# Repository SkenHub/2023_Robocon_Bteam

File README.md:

# 2023_Robocon_Bteam
2023年高専ロボコン「もぎもぎ！フルーツＧＯラウンド」Bチーム
## メンバー
*  機械　ヒロハタ，金子，入谷，斉藤，神鍋 ,今井
*  制御　野口，川崎，笹渕，川口，黒住，佐谷  
*  回路　中井，岩井　
*  1年　北嶋，真志取  
* メイン：野口、川崎，金子
* ピット：渡邉，入谷，北嶋，廣畑，真志取

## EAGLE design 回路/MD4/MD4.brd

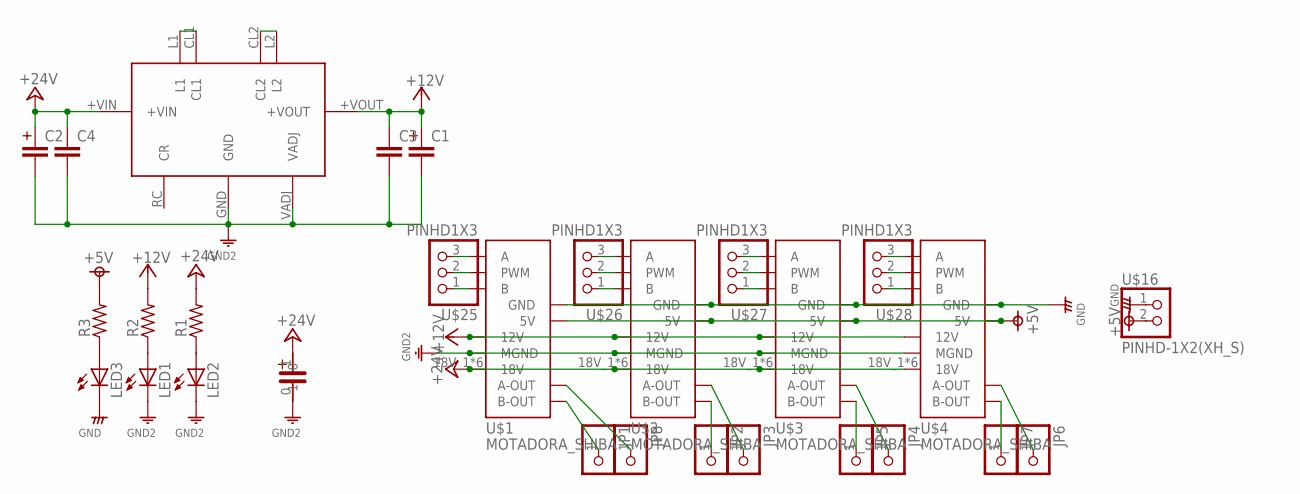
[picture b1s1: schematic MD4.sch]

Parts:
C1, C2: CAPACITOR-1U; C_1U
C3, C4: MLCC-5; MLCC_50
CAPACITOR1: CAPACITOR
JP1, JP2, JP3, JP4, JP5, JP6, JP7, JP8: PINHD-1X1; 1X01
LED1, LED2, LED3: LED3MM
R1, R2, R3: RESISTORS-3; R_0.3
U$1, U$2, U$3, U$4: MOTADORA_SHIBA
U$10: HPH12002M
U$16: PINHD-1X2(XH_S); 1X2(XH-S)
U$25, U$26, U$27, U$28: PINHD1X3; 1X3(XH)

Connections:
+5V: R3.2, U$1.5V, U$1.5V_2 (5V), U$2.5V, U$2.5V_2 (5V), U$3.5V, U$3.5V_2 (5V), U$4.5V, U$4.5V_2 (5V), U$16.2
+12V: C1.P$1 (1), C3.1, R2.2, U$1.12V_1 (12V), U$1.12V_2 (12V), U$1.12V_3 (12V), U$1.12V_4 (12V), U$1.12V_5 (12V), U$1.12V_6 (12V), U$2.12V_1 (12V), U$2.12V_2 (12V), U$2.12V_3 (12V), U$2.12V_4 (12V), U$2.12V_5 (12V), U$2.12V_6 (12V), U$3.12V_1 (12V), U$3.12V_2 (12V), U$3.12V_3 (12V), U$3.12V_4 (12V), U$3.12V_5 (12V), U$3.12V_6 (12V), U$4.12V_1 (12V), U$4.12V_2 (12V), U$4.12V_3 (12V), U$4.12V_4 (12V), U$4.12V_5 (12V), U$4.12V_6 (12V), U$10.+VOUT
GND: LED3.K (C), U$1.GND, U$1.GND2 (GND), U$2.GND, U$2.GND2 (GND), U$3.GND, U$3.GND2 (GND), U$4.GND, U$4.GND2 (GND), U$16.1
GND12: C1.P$2 (2), C2.P$2 (2), C3.2, C4.2, CAPACITOR1.0, LED1.K (C), LED2.K (C), U$1.MGND_1 (MGND), U$1.MGND_2 (MGND), U$1.MGND_3 (MGND), U$1.MGND_4 (MGND), U$1.MGND_5 (MGND), U$1.MGND_6 (MGND), U$2.MGND_1 (MGND), U$2.MGND_2 (MGND), U$2.MGND_3 (MGND), U$2.MGND_4 (MGND), U$2.MGND_5 (MGND), U$2.MGND_6 (MGND), U$3.MGND_1 (MGND), U$3.MGND_2 (MGND), U$3.MGND_3 (MGND), U$3.MGND_4 (MGND), U$3.MGND_5 (MGND), U$3.MGND_6 (MGND), U$4.MGND_1 (MGND), U$4.MGND_2 (MGND), U$4.MGND_3 (MGND), U$4.MGND_4 (MGND), U$4.MGND_5 (MGND), U$4.MGND_6 (MGND), U$10.GND, U$10.VADJ
unnamed: JP1.1, U$1.B-OUT_1 (B-OUT), U$1.B-OUT_2 (B-OUT), U$1.B-OUT_3 (B-OUT), U$1.B-OUT_4 (B-OUT), U$1.B-OUT_5 (B-OUT), U$1.B-OUT_6 (B-OUT)
unnamed: JP3.1, U$2.A-OUT_1 (A-OUT), U$2.A-OUT_2 (A-OUT), U$2.A-OUT_3 (A-OUT), U$2.A-OUT_4 (A-OUT), U$2.A-OUT_5 (A-OUT), U$2.A-OUT_6 (A-OUT)
unnamed: JP4.1, U$3.A-OUT_1 (A-OUT), U$3.A-OUT_2 (A-OUT), U$3.A-OUT_3 (A-OUT), U$3.A-OUT_4 (A-OUT), U$3.A-OUT_5 (A-OUT), U$3.A-OUT_6 (A-OUT)
unnamed: JP5.1, U$3.B-OUT_1 (B-OUT), U$3.B-OUT_2 (B-OUT), U$3.B-OUT_3 (B-OUT), U$3.B-OUT_4 (B-OUT), U$3.B-OUT_5 (B-OUT), U$3.B-OUT_6 (B-OUT)
unnamed: JP7.1, U$4.B-OUT_1 (B-OUT), U$4.B-OUT_2 (B-OUT), U$4.B-OUT_3 (B-OUT), U$4.B-OUT_4 (B-OUT), U$4.B-OUT_5 (B-OUT), U$4.B-OUT_6 (B-OUT)
unnamed: JP8.1, U$1.A-OUT_1 (A-OUT), U$1.A-OUT_2 (A-OUT), U$1.A-OUT_3 (A-OUT), U$1.A-OUT_4 (A-OUT), U$1.A-OUT_5 (A-OUT), U$1.A-OUT_6 (A-OUT)
unnamed: U$1.B, U$1.B2 (B), U$25.1
unnamed: U$1.PWM, U$1.PWM2 (PWM), U$25.2
unnamed: U$1.A, U$1.A2 (A), U$25.3
unnamed: U$2.B, U$2.B2 (B), U$26.1
unnamed: U$2.PWM, U$2.PWM2 (PWM), U$26.2
unnamed: U$2.A, U$2.A2 (A), U$26.3
unnamed: U$3.B, U$3.B2 (B), U$27.1
unnamed: U$3.PWM, U$3.PWM2 (PWM), U$27.2
unnamed: U$3.A, U$3.A2 (A), U$27.3
unnamed: U$4.B, U$4.B2 (B), U$28.1
unnamed: U$4.PWM, U$4.PWM2 (PWM), U$28.2
unnamed: U$4.A, U$4.A2 (A), U$28.3
unnamed: LED2.A, R1.1
unnamed: U$10.CL2, U$10.L2
unnamed: U$10.CL1, U$10.L1
unnamed: LED1.A, R2.1
unnamed: LED3.A, R3.1
unnamed: JP6.1, U$4.A-OUT_1 (A-OUT), U$4.A-OUT_2 (A-OUT), U$4.A-OUT_3 (A-OUT), U$4.A-OUT_4 (A-OUT), U$4.A-OUT_5 (A-OUT), U$4.A-OUT_6 (A-OUT)
unnamed: JP2.1, U$2.B-OUT_1 (B-OUT), U$2.B-OUT_2 (B-OUT), U$2.B-OUT_3 (B-OUT), U$2.B-OUT_4 (B-OUT), U$2.B-OUT_5 (B-OUT), U$2.B-OUT_6 (B-OUT)
unnamed: C2.P$1 (1), C4.1, CAPACITOR1.1, R1.2, U$1.18V_1 (18V), U$1.18V_2 (18V), U$1.18V_3 (18V), U$1.18V_4 (18V), U$1.18V_5 (18V), U$1.18V_6 (18V), U$2.18V_1 (18V), U$2.18V_2 (18V), U$2.18V_3 (18V), U$2.18V_4 (18V), U$2.18V_5 (18V), U$2.18V_6 (18V), U$3.18V_1 (18V), U$3.18V_2 (18V), U$3.18V_3 (18V), U$3.18V_4 (18V), U$3.18V_5 (18V), U$3.18V_6 (18V), U$4.18V_1 (18V), U$4.18V_2 (18V), U$4.18V_3 (18V), U$4.18V_4 (18V), U$4.18V_5 (18V), U$4.18V_6 (18V), U$10.+VIN

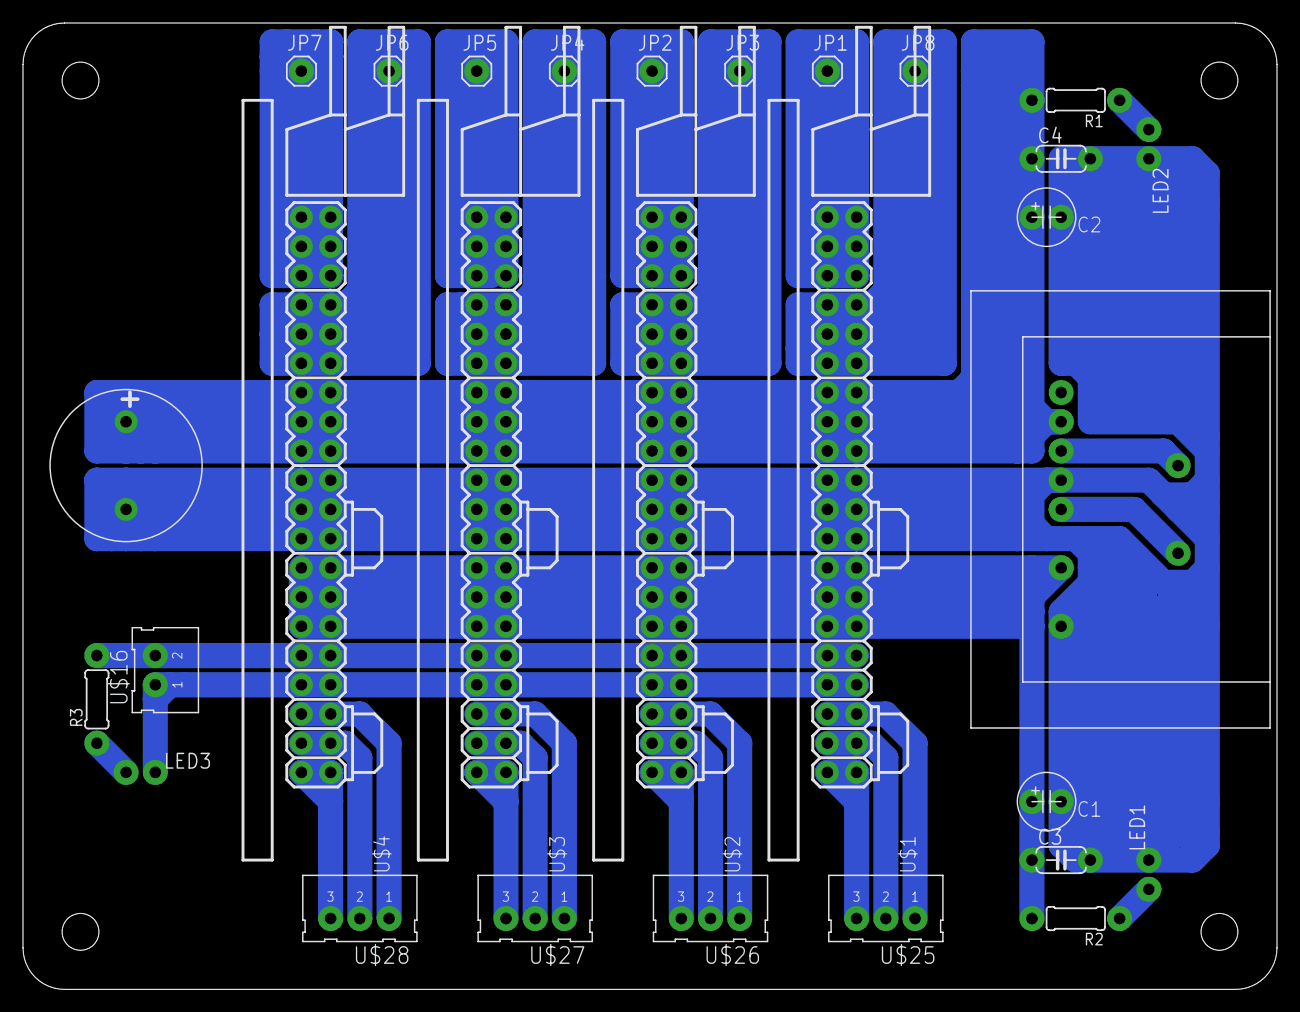
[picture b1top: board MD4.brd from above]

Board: 2 copper layers, 109.0 x 84.0 mm, 29 parts (0 on the bottom side), 30 nets.

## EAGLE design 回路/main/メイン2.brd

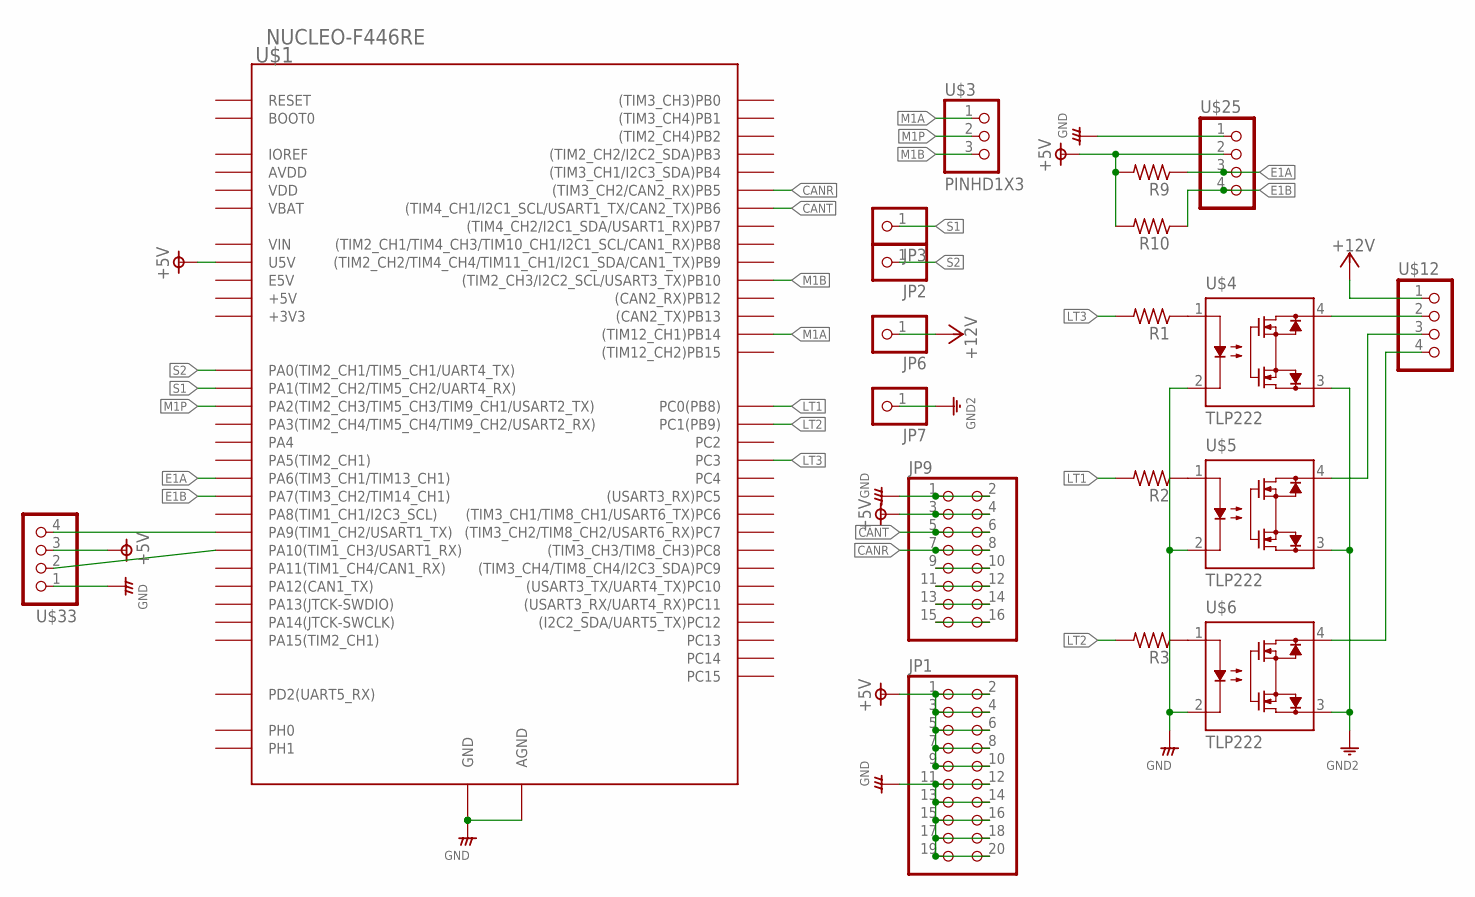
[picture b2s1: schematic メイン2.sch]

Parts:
JP1: PINHD-2X10; 2X10
JP2, JP3, JP6, JP7: PINHD-1X1; 1X01
JP9: PINHD-2X8; 2X08
R1, R2, R3, R9, R10: RESISTORS-3; R_0.3
U$1: NUCLEO-F446RE; NUCLEO-F（L）ｘｘｘRｘ
U$3: PINHD1X3; 1X3(XH)
U$4, U$5, U$6: TLP222; DIP4
U$12, U$25, U$33: XH-PIN4; XH-4PIN

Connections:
+5V: JP1.1, JP1.2, JP1.3, JP1.4, JP1.5, JP1.6, JP1.7, JP1.8, JP1.9, JP1.10, JP9.3, JP9.4, R9.2, R10.2, U$1.U5V, U$25.2, U$33.3
+12V: JP6.1, U$12.1
CANR: JP9.7, JP9.8, U$1.PB5 ((TIM3_CH2/CAN2_RX)PB5)
CANT: JP9.5, JP9.6, U$1.PB6 ((TIM4_CH1/I2C1_SCL/USART1_TX/CAN2_TX)PB6)
E1A: R9.1, U$1.PA6 (PA6(TIM3_CH1/TIM13_CH1)), U$25.3
E1B: R10.1, U$1.PA7 (PA7(TIM3_CH2/TIM14_CH1)), U$25.4
GND: JP1.11, JP1.12, JP1.13, JP1.14, JP1.15, JP1.16, JP1.17, JP1.18, JP1.19, JP1.20, JP9.1, JP9.2, U$1.AGND, U$1.GND@1 (GND), U$1.GND@2 (GND), U$1.GND@3 (GND), U$1.GND@4 (GND), U$1.GND@5 (GND), U$1.GND@6 (GND), U$4.2 (2CATHODE), U$5.2 (2CATHODE), U$6.2 (2CATHODE), U$25.1, U$33.1
GND12: JP7.1, U$4.3 (3DRAIN), U$5.3 (3DRAIN), U$6.3 (3DRAIN)
LT1: R2.2, U$1.PC0 (PC0(PB8))
LT2: R3.2, U$1.PC1 (PC1(PB9))
LT3: R1.2, U$1.PC3
M1A: U$1.PB14 ((TIM12_CH1)PB14), U$3.1
M1B: U$1.PB10 ((TIM2_CH3/I2C2_SCL/USART3_TX)PB10), U$3.3
M1P: U$1.PA2 (PA2(TIM2_CH3/TIM5_CH3/TIM9_CH1/USART2_T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), U$3.2
unnamed: U$1.PA10 (PA10(TIM1_CH3/USART1_RX)), U$33.2
unnamed: U$1.PA9 (PA9(TIM1_CH2/USART1_TX)), U$33.4
unnamed: U$4.4 (4DRAIN), U$12.2
unnamed: U$5.4 (4DRAIN), U$12.3
unnamed: U$6.4 (4DRAIN), U$12.4
unnamed: JP9.9, JP9.10
unnamed: JP9.11, JP9.12
unnamed: JP9.13, JP9.14
unnamed: JP9.15, JP9.16
unnamed: R1.1, U$4.1 (1ANODE)
unnamed: R2.1, U$5.1 (1ANODE)
unnamed: R3.1, U$6.1 (1ANODE)
S1: JP3.1, U$1.PA1 (PA1(TIM2_CH2/TIM5_CH2/UART4_RX))
S2: JP2.1, U$1.PA0 (PA0(TIM2_CH1/TIM5_CH1/UART4_TX))

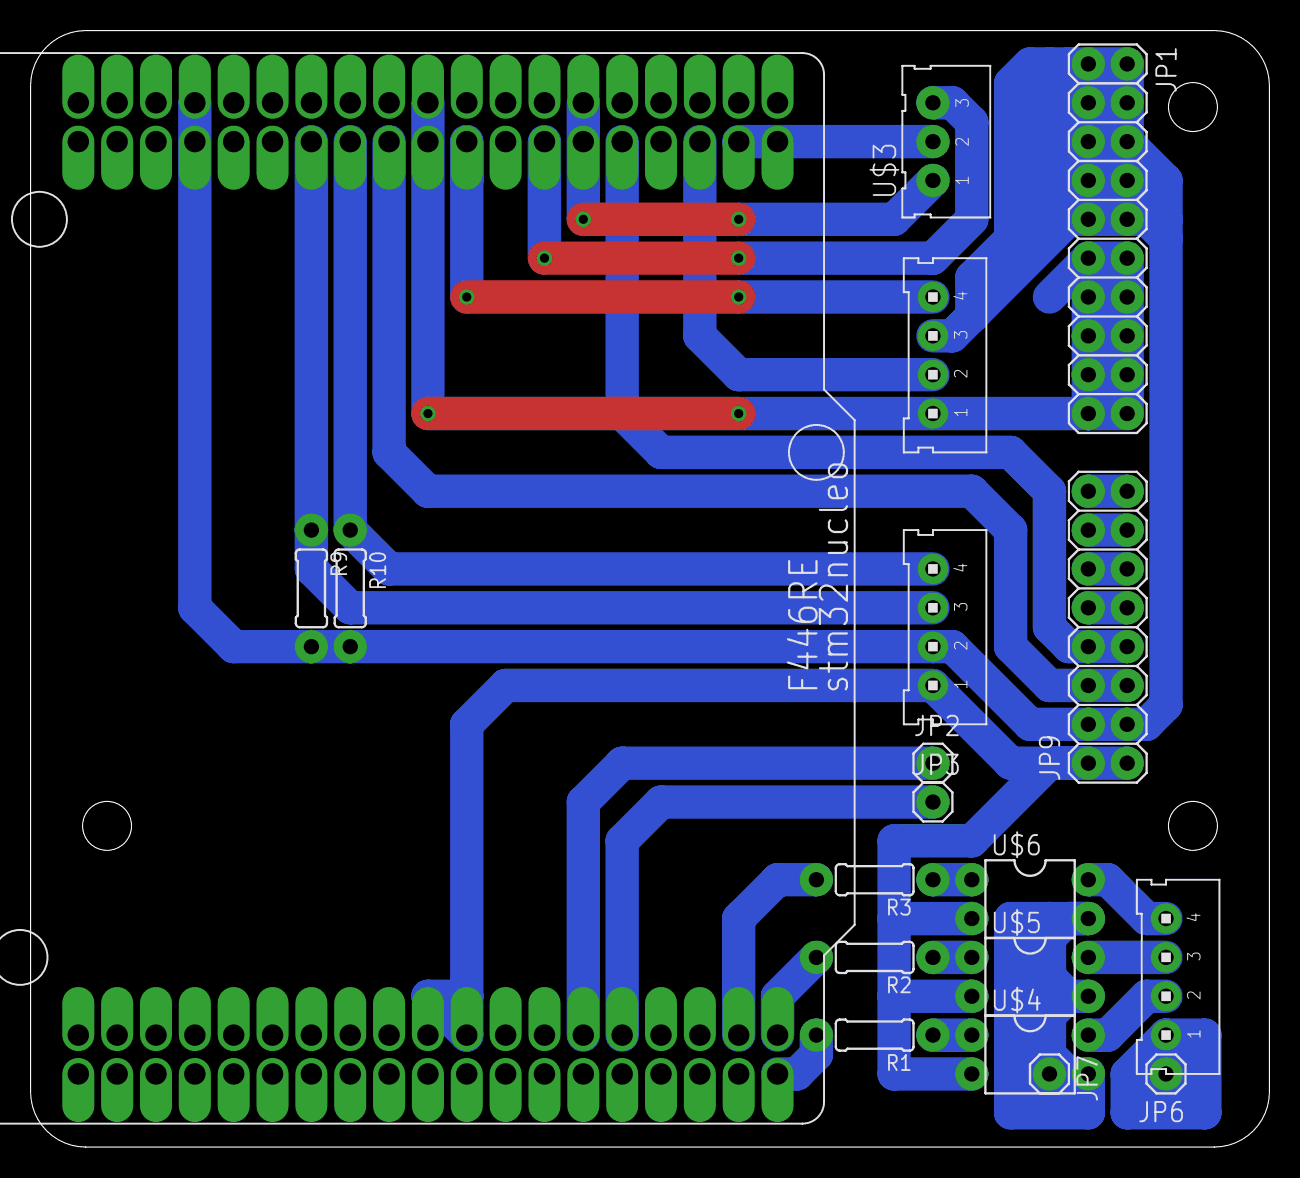
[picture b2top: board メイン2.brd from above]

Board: 2 copper layers, 81.0 x 73.0 mm, 19 parts (0 on the bottom side), 28 nets.

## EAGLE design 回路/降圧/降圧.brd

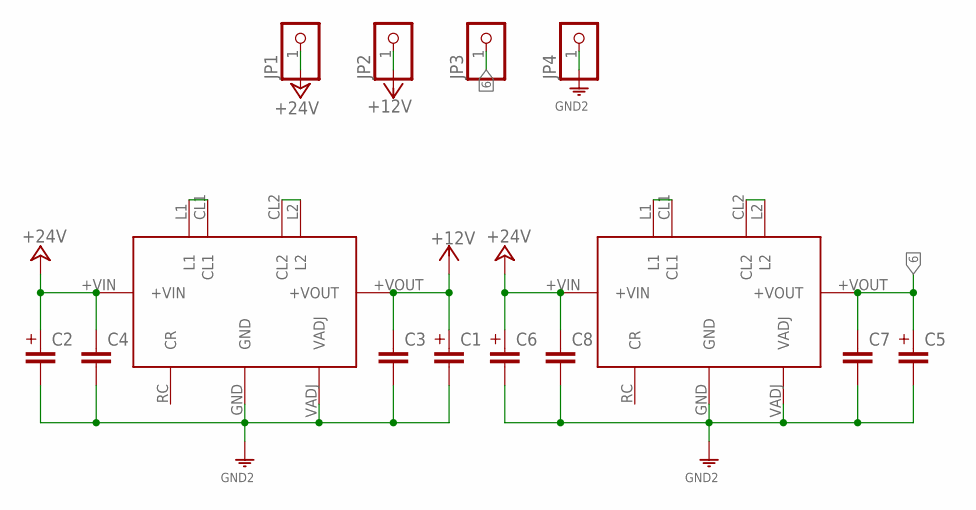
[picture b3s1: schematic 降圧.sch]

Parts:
C1, C2, C5, C6: CAPACITOR-1U; C_1U
C3, C4, C7, C8: MLCC-5; MLCC_50
JP1, JP2, JP3, JP4: PINHD-1X1; 1X01
U$1, U$4: HPH12002M

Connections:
6: C5.P$1 (1), C7.1, JP3.1, U$4.+VOUT
+12V: C1.P$1 (1), C3.1, JP2.1, U$1.+VOUT
+24V: C2.P$1 (1), C4.1, C6.P$1 (1), C8.1, JP1.1, U$1.+VIN, U$4.+VIN
GND: C1.P$2 (2), C2.P$2 (2), C3.2, C4.2, C5.P$2 (2), C6.P$2 (2), C7.2, C8.2, JP4.1, U$1.GND, U$1.VADJ, U$4.GND, U$4.VADJ
unnamed: U$1.CL1, U$1.L1
unnamed: U$1.CL2, U$1.L2
unnamed: U$4.CL1, U$4.L1
unnamed: U$4.CL2, U$4.L2

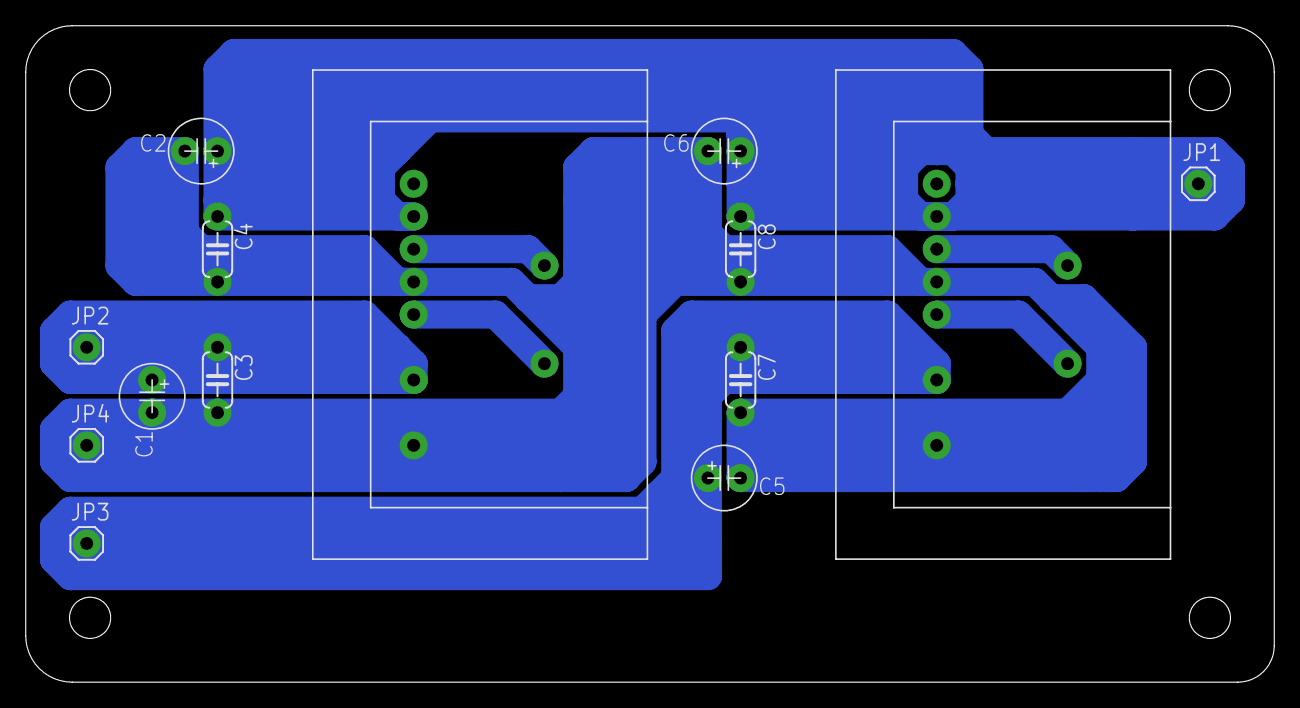
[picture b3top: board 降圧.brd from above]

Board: 2 copper layers, 97.0 x 51.0 mm, 14 parts (0 on the bottom side), 8 nets.

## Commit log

2023-06-08 Create 機械
2023-06-08 Add files via upload
    ジャイロセンサー プログラム
2023-06-08 realsenseロボットのテストプログラム
    ロボットの旋回中心とrealsenseの中心の差を考慮
2023-06-08 テストロボット（足回り）のプログラム
2023-06-25 Create LED
2023-06-30 ヨー軸のシリアル通信出力
    ヨー軸の実数値（０～360度）を共用体で4バイト出力．
    先頭2バイトはHEX A0A0 で計6バイト
2023-06-30 Update wit901_1.ino
    oledディスプレイ搭載
2023-06-30 Update wit901_1.ino
    エラー修正
2023-06-30 Update wit901_1.ino
    表示をええ感じに
2023-06-30 パワーウィンドウからメカナムへ変更
2023-07-08 メカナム足回り
    PS3はSBDBTを使ってね
2023-07-10 Create unity
2023-08-20 完成形足回りプログラム
2023-08-27 収穫機構プログラムVer3制作
2023-08-30 get_V3のパラメータ調整
2023-10-03 足回りプログラム完成版
2023-10-03 ルールブックとFAQ
2023-10-05 足回りプログラム更新
    146行目の数字がモータのpwmだよ
2023-10-11 鋼鶴天翔の完成形
    改善の余地あり(悪足掻き)
